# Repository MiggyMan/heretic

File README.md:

# heretic

My take on the infidel sensor

Forked from https://github.com/drspangle/infidel-sensor

# Original readme below

# Inline Filament Diameter Estimator, Lowcost (InFiDEL)

<p xmlns:dct="http://purl.org/dc/terms/" xmlns:vcard="http://www.w3.org/2001/vcard-rdf/3.0#">
  
  Originally created by Thomas Sanladerer
</p>

*A cheap, yet precise filament diameter sensor, intended to compensate for filament diameter deviations in real-time.*

The InFiDEL is a cheap (< $5) filament diameter sensor intended for use with FDM 3d printers.
The sensor can be calibrated to provide surprisingly precise filament diameter readings in real-time. 
The main idea is to use the sensor to correct for filament diameter deviations while printing.

Based on this proof-of-concept: https://www.youmagine.com/designs/filament-diameter-sensor

## Assembly and Setup

### Calibration
- Flash board with calibration.ino
- Connect a host via I2C (see provided host-example.ino)
- Insert each calibration drill bit shafts and replace the lookup table entries in driver.ino with your own measurements
  * Measure the actual diameter of the shafts and fill second column
  * Use the host's output *1000 to fill first column
- Finally, flash driver.ino with your values filled out
- Hub should now output exact diameter values

#### Note:
Analog output is currently not enabled in driver.ino (I2C and FAULT pin only)

## BOM

### Printed Parts
1 Block
1 Lever

#### Note:
Parts should preferably be printed in PETG, ABS or ASA as PLA may creep significantly over time.

### Electronics
There are two board variants included in this repository, either can be used to assemble the InFiDEL.

Choose one:
- SMT control board (which is populated; Gerber files and component specifications are included) 
- THT control board

Also required:

- Suitable programmer for ATTiny85 (eg USBtinyISP)
- 1 SS495A linear hall effect sensor (or comparable)

### Fasteners
- 2 M3x8 screws (eg ISO 4762 M2x8)
- 1 3x24mm pin (eg DIN 7 3x24mm, for mating lever to the block)
- 1 3x16mm pin (eg DIN 7 3x16mm, for roller bearing in lever)
- 1 3x18mm pin (eg DIN 7 3x18mm, for idler bearing in block)
- 6 M3 threaded inserts

Pins may be replaced with screws or grubscrews, which may result in decreased precision.

### Other Hardware
- 1 6x2mm magnet (eg N35)
- 4 623 bearings (preferably 623-2Z / 623-ZZ)
- 1 Ballpoint pen spring (or other soft 4mm spring)
- Short length of PTFE tube

### Calibration Accessories
- 1 1.5mm drill bit
- 1 1.7mm or 1.8mm drill bit 
- 1 2mm drill bit
- Calipers for verifying drill bit shaft diameter

Drill bits may be replaced with similar diameters. 
Measured diameter is to be written to firmware lookup table.

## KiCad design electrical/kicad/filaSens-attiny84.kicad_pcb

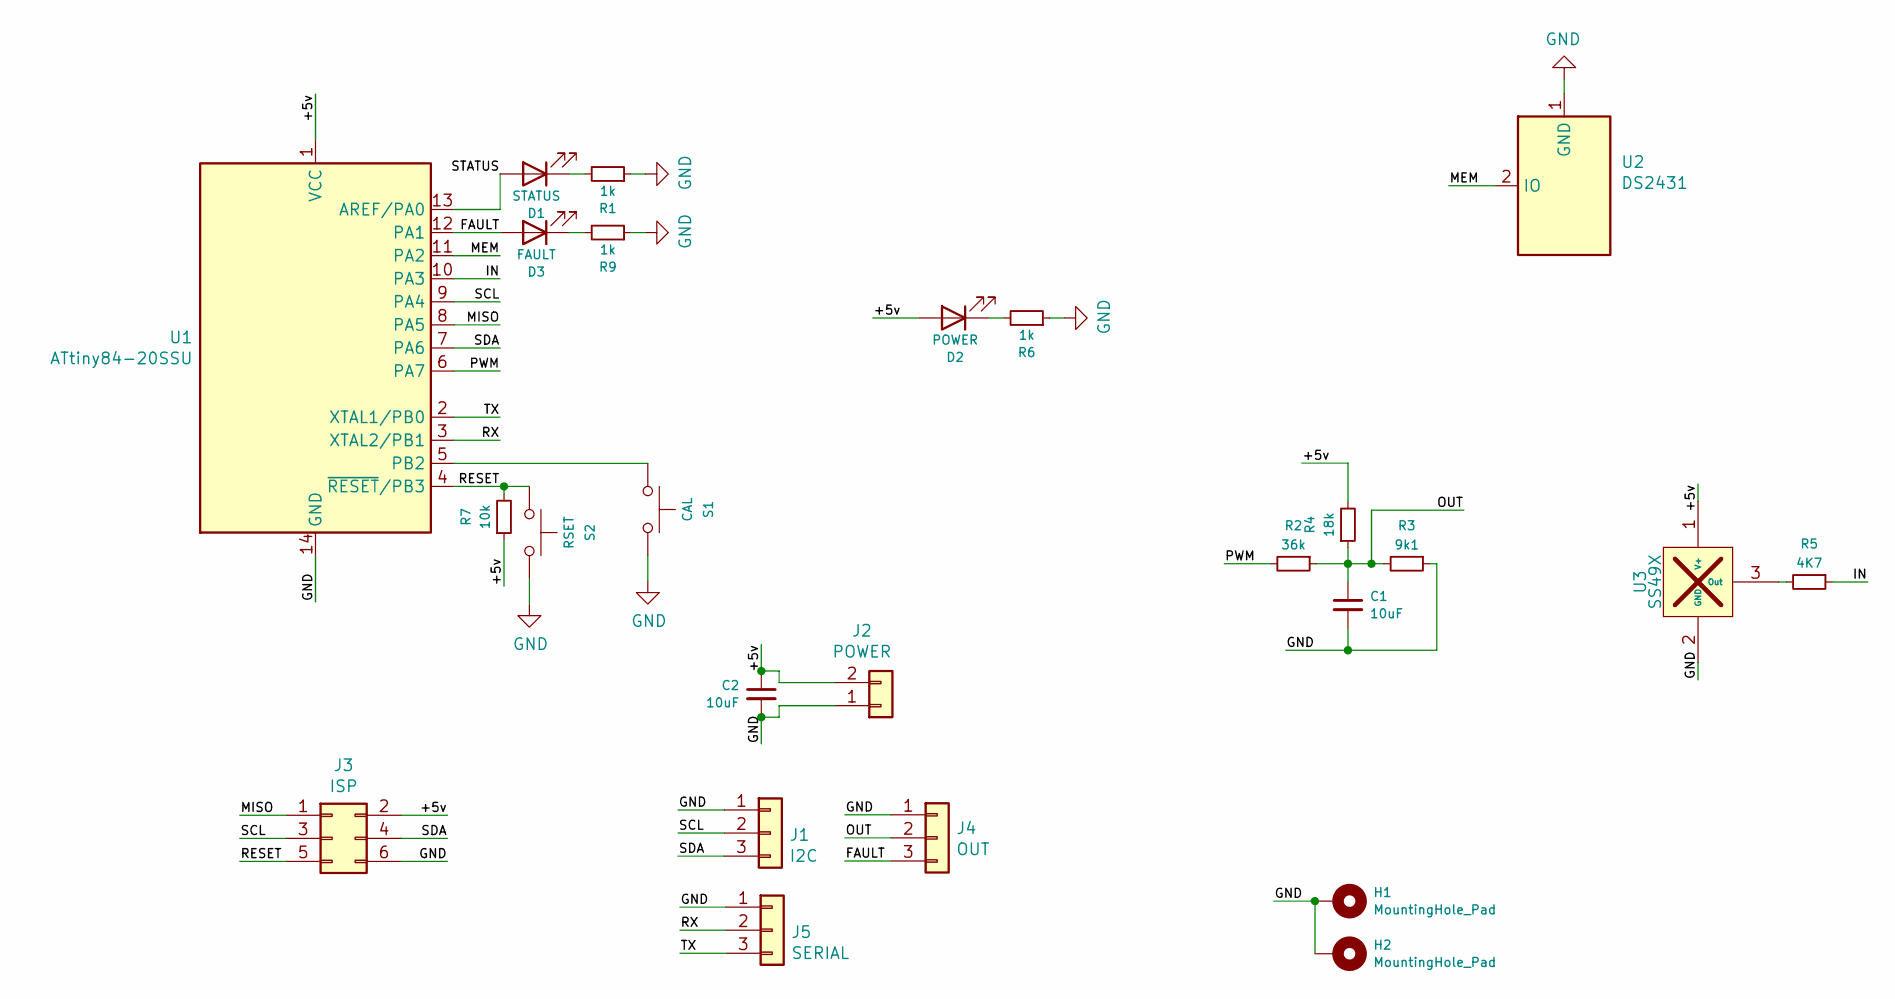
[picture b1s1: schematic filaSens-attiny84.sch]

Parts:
C1, C2: 10uF; C_0603_1608Metric_Pad1.05x0.95mm_HandSolder; LCSC C19702
D1: STATUS; LED_0603_1608Metric_Pad1.05x0.95mm_HandSolder; LCSC C72041
D2: POWER; LED_0603_1608Metric_Pad1.05x0.95mm_HandSolder; LCSC C72043
D3: FAULT; LED_0603_1608Metric_Pad1.05x0.95mm_HandSolder; LCSC C72038
H1, H2: MountingHole_Pad; MountingHole_3.2mm_M3_ISO14580_Pad
J1: I2C; PinHeader_1x03_P2.54mm_Vertical
J2: POWER; PinHeader_1x02_P2.54mm_Vertical
J3: ISP; PinHeader_2x03_P2.54mm_Vertical
J4: OUT; PinHeader_1x03_P2.54mm_Vertical
J5: SERIAL; PinHeader_1x03_P2.54mm_Vertical
R1, R6, R9: 1k; R_0402_1005Metric_Pad0.72x0.64mm_HandSolder; LCSC C11702
R2: 36k; R_0402_1005Metric_Pad0.72x0.64mm_HandSolder; LCSC C25783
R3: 9k1; R_0402_1005Metric_Pad0.72x0.64mm_HandSolder; LCSC C25926
R4: 18k; R_0402_1005Metric_Pad0.72x0.64mm_HandSolder; LCSC C25762
R5: 4K7; R_Axial_DIN0204_L3.6mm_D1.6mm_P2.54mm_Vertical; LCSC C25900
R7: 10k; R_0402_1005Metric_Pad0.72x0.64mm_HandSolder; LCSC C25744
S1: CAL; SW_Push_1P1T_NO_6x6mm_H9.5mm; LCSC C127509
S2: RSET; SW_Push_1P1T_NO_6x6mm_H9.5mm; LCSC C127509
U1: ATtiny84-20SSU; SOIC-14_3.9x8.7mm_P1.27mm; LCSC C144333
U2: DS2431; TSOC-6_3.76x3.94mm_P1.27mm; LCSC C9387
U3: SS49X; TO-92Flat

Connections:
/+5v: C2.1, D2.2 (A), J2.2, J3.2, R4.2, R7.1, U1.1 (VCC), U3.1 (V+)
/FAULT: D3.2 (A), J4.3, U1.12 (PA1)
/IN: R5.1, U1.10 (PA3)
/MEM: U1.11 (PA2), U2.2 (IO)
/MISO: J3.1, U1.8 (PA5)
/OUT: C1.1, J4.2, R2.1, R3.2, R4.1
/PWM: R2.2, U1.6 (PA7)
/RESET: J3.5, R7.2, S2.1, U1.4 (~RESET~/PB3)
/RX: J5.2, U1.3 (XTAL2/PB1)
/SCL: J1.2, J3.3, U1.9 (PA4)
/SDA: J1.3, J3.4, U1.7 (PA6)
/STATUS: D1.2 (A), U1.13 (AREF/PA0)
/TX: J5.3, U1.2 (XTAL1/PB0)
GND: C1.2, C2.2, H1.1, H2.1, J1.1, J2.1, J3.6, J4.1, J5.1, R1.1, R3.1, R6.1, R9.1, S1.2, S2.2, U1.14 (GND), U2.1 (GND), U3.2 (GND)
unnamed: D1.1 (K), R1.2
unnamed: D2.1 (K), R6.2
unnamed: D3.1 (K), R9.2
unnamed: R5.2, U3.3 (Out)
unnamed: S1.1, U1.5 (PB2)

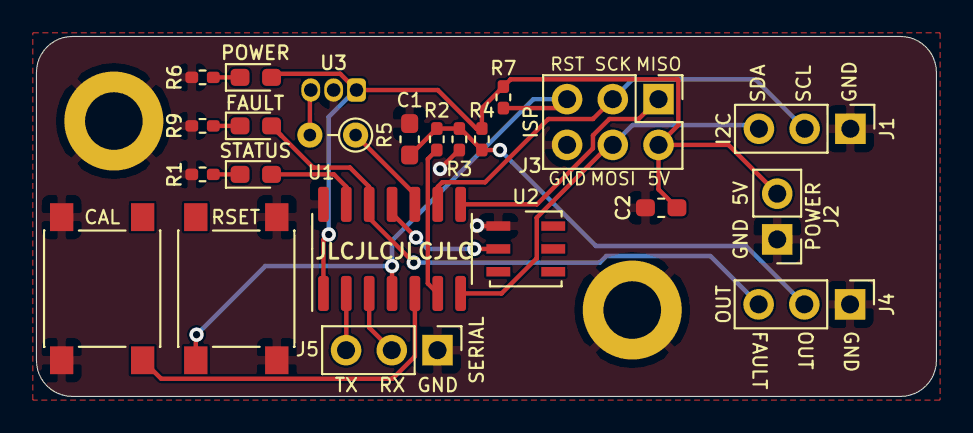
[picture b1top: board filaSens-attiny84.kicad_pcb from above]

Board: 2 copper layers, 50.0 x 20.0 mm, 25 parts (0 on the bottom side), 19 nets.

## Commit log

2021-03-10 Initial import, at this point only the electricalide of things differs.
2021-03-11 * Removed DS2402, twas a silly choice for a board with the option of being an i2c slave * Updated silkscreen for better readability * Added DS2431 one wire eeprom to replace the i2c one * Moved STATU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
2021-03-19 * Split output headers into serial/i2c/analogue/power * Rearranged i2c/analouge/power headers to better fit horizontal pin headers * Made R5 throughole to make it easier to change and experiment with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
2021-03-20 * Updated the block model for v0.3 board layout * Updated gerbers, bom and placement files

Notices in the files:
README.md:
href="http://creativecommons.org/publicdomain/zero/1.0/">
CC0
electrical/kicad/filaSens-attiny84.kicad_pcb:
Licensed as Public Domain
